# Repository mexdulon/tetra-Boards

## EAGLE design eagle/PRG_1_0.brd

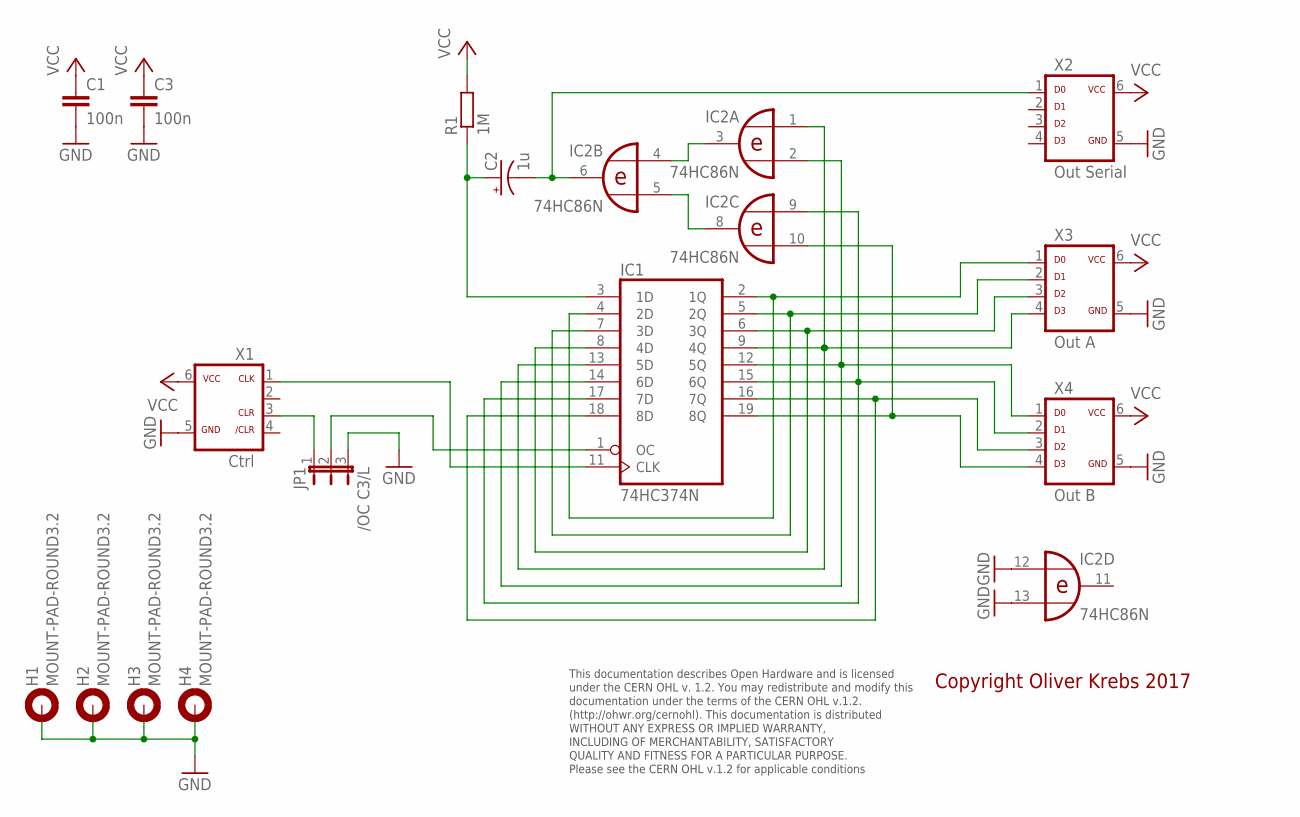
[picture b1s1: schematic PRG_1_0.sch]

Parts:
C1, C3: 100n; C050-025X075
C2: 1u; CPOL-RADIAL-10UF-25V
H1, H2, H3, H4: MOUNT-PAD-ROUND3.2; 3,2-PAD
IC1: 74HC374N; DIL20
IC2: 74HC86N; DIL14
JP1: /OC C3/L; JP2-U
R1: 1M; 0207/10
X1: Ctrl; ML-6
X2: Out Serial; ML-6
X3: Out A; ML-6
X4: Out B; ML-6

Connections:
GND: C1.2, C3.2, H1.B3,2, H2.B3,2, H3.B3,2, H4.B3,2, IC1.10 (GND), IC2.7 (GND), IC2.12 (I0), IC2.13 (I1), JP1.3, X1.5, X2.5, X3.5, X4.5
unnamed: IC2.3 (O), IC2.4 (I0)
unnamed: IC2.5 (I1), IC2.8 (O)
unnamed: C2.2 (-), IC2.6 (O), X2.1
unnamed: C2.1 (+), IC1.3 (1D), R1.1
unnamed: IC1.11 (CLK), X1.1
unnamed: IC1.1 (OC), JP1.2
unnamed: IC1.2 (1Q), IC1.4 (2D), X3.1
unnamed: IC1.5 (2Q), IC1.7 (3D), X3.2
unnamed: IC1.6 (3Q), IC1.8 (4D), X3.3
unnamed: IC1.9 (4Q), IC1.13 (5D), IC2.1 (I0), X3.4
unnamed: IC1.12 (5Q), IC1.14 (6D), IC2.2 (I1), X4.1
unnamed: IC1.15 (6Q), IC1.17 (7D), IC2.9 (I0), X4.2
unnamed: IC1.16 (7Q), IC1.18 (8D), X4.3
unnamed: IC1.19 (8Q), IC2.10 (I1), X4.4
unnamed: JP1.1, X1.3
VCC: C1.1, C3.1, IC1.20 (VCC), IC2.14 (VCC), R1.2, X1.6, X2.6, X3.6, X4.6

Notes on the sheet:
This documentation describes Open Hardware and is licensed under the CERN OHL v. 1.2. You may redistribute and modify this documentation under the terms of the CERN OHL v.1.2. (http://ohwr.org/cernohl). This documentation is distributed WITHOUT ANY EXPRESS OR IMPLIED WARRANTY, INCLUDING OF MERCHANT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
Copyright Oliver Krebs 2017

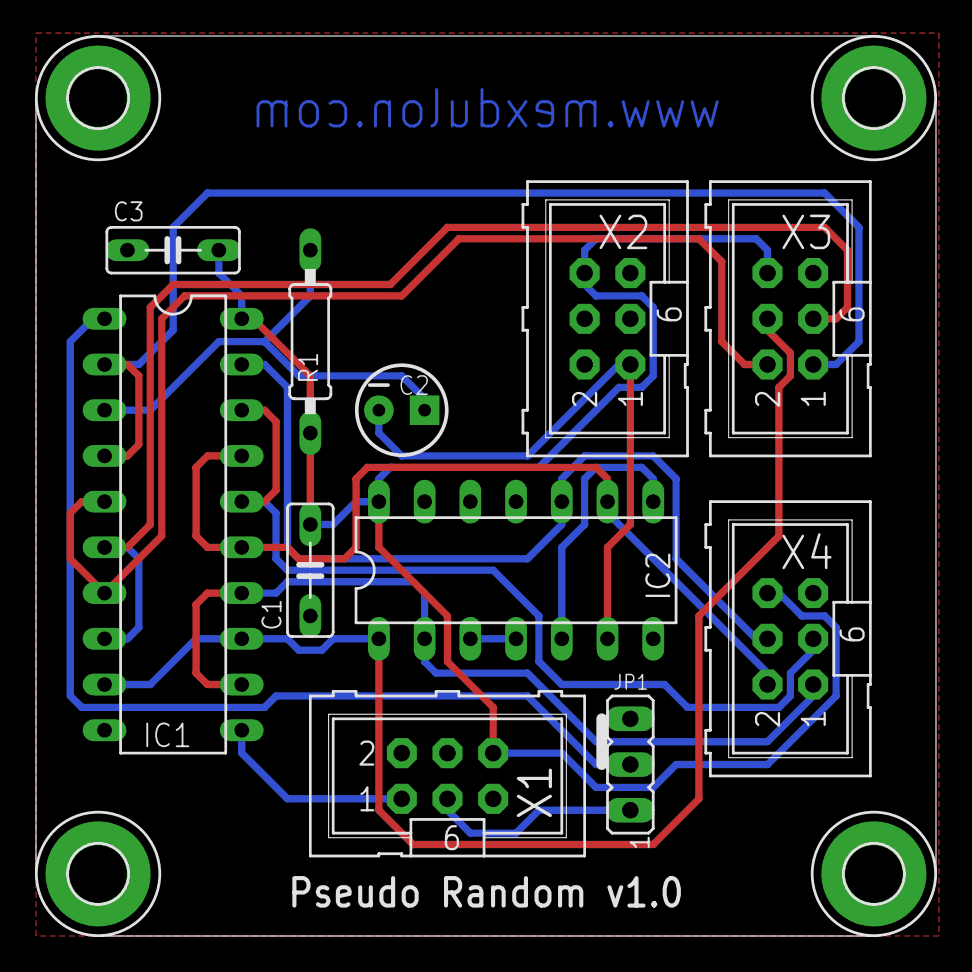
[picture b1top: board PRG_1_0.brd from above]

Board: 2 copper layers, 50.0 x 50.0 mm, 15 parts (0 on the bottom side), 17 nets.

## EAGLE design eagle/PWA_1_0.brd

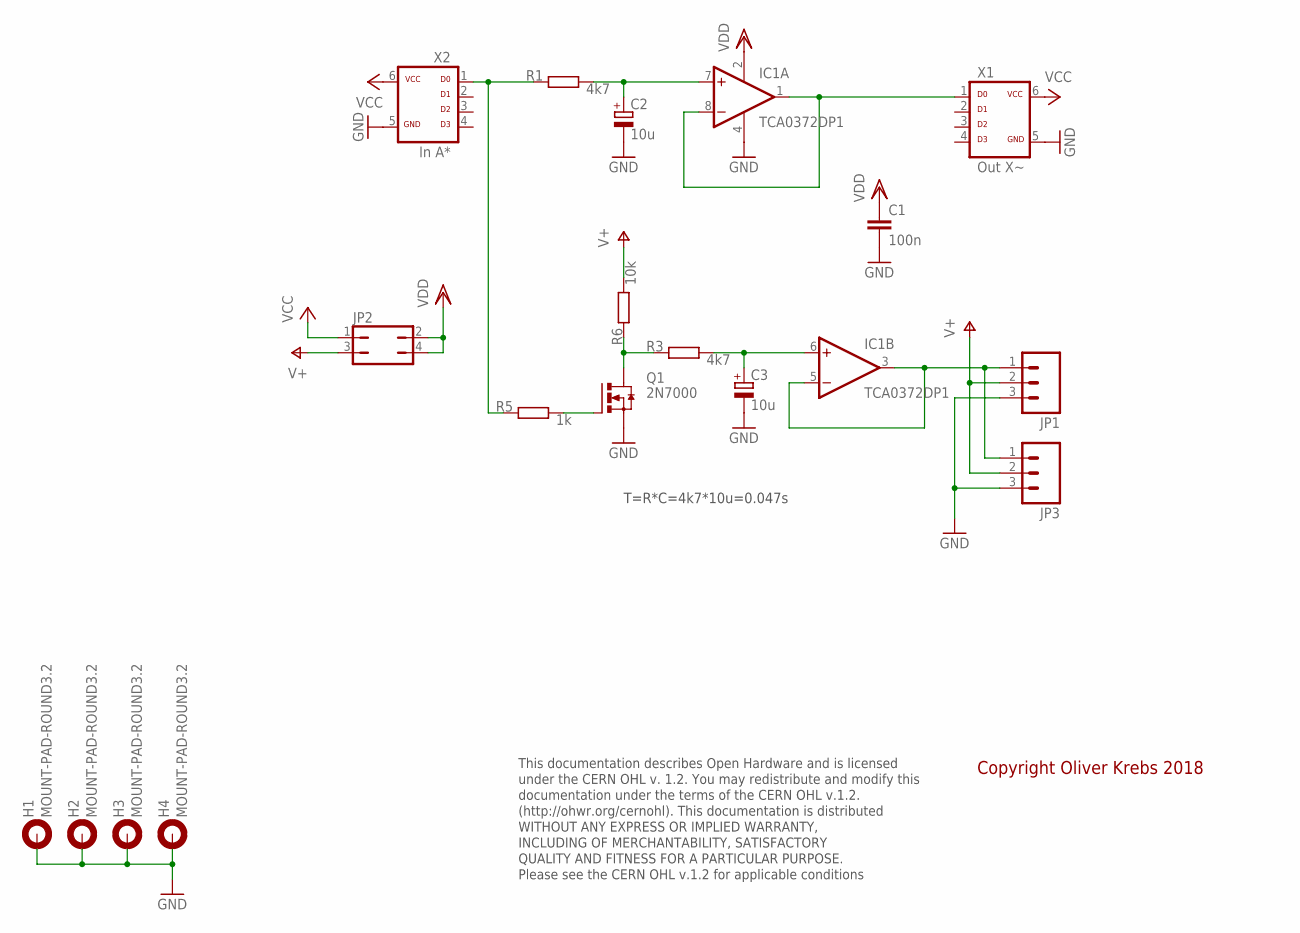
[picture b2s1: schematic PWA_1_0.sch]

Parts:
C1: 100n; C050-025X075
C2, C3: 10u; E2-4
H1, H2, H3, H4: MOUNT-PAD-ROUND3.2; 3,2-PAD
IC1: TCA0372DP1; DIL08
JP1: M03PTH; 1X03
JP2: JP2Q
JP3: M03BIG_5.08; 1X03_BIG_5.08
Q1: 2N7000; TO92-LINE
R1, R3: 4k7; 0207/10
R5: 1k; 0207/10
R6: 10k; 0207/10
X1: Out X~; ML-6
X2: In A*; ML-6

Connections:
GND: C1.2, C2.-, C3.-, H1.B3,2, H2.B3,2, H3.B3,2, H4.B3,2, IC1.4 (GND), JP1.3, JP3.3, Q1.3 (S), X1.5, X2.5
unnamed: C2.+, IC1.7 (+IN), R1.2
unnamed: IC1.1 (OUT), IC1.8 (-IN), X1.1
unnamed: R1.1, R5.1, X2.1
unnamed: IC1.3 (OUT), IC1.5 (-IN), JP1.1, JP3.1
unnamed: C3.+, IC1.6 (+IN), R3.2
unnamed: Q1.1 (D), R3.1, R6.1
unnamed: Q1.2 (G), R5.2
V+: JP1.2, JP2.3, JP3.2, R6.2
VCC: JP2.1, X1.6, X2.6
VDD: C1.1, IC1.2 (VDD), JP2.2, JP2.4

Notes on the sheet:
This documentation describes Open Hardware and is licensed under the CERN OHL v. 1.2. You may redistribute and modify this documentation under the terms of the CERN OHL v.1.2. (http://ohwr.org/cernohl). This documentation is distributed WITHOUT ANY EXPRESS OR IMPLIED WARRANTY, INCLUDING OF MERCHANT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
Copyright Oliver Krebs 2018
T=R*C=4k7*10u=0.047s

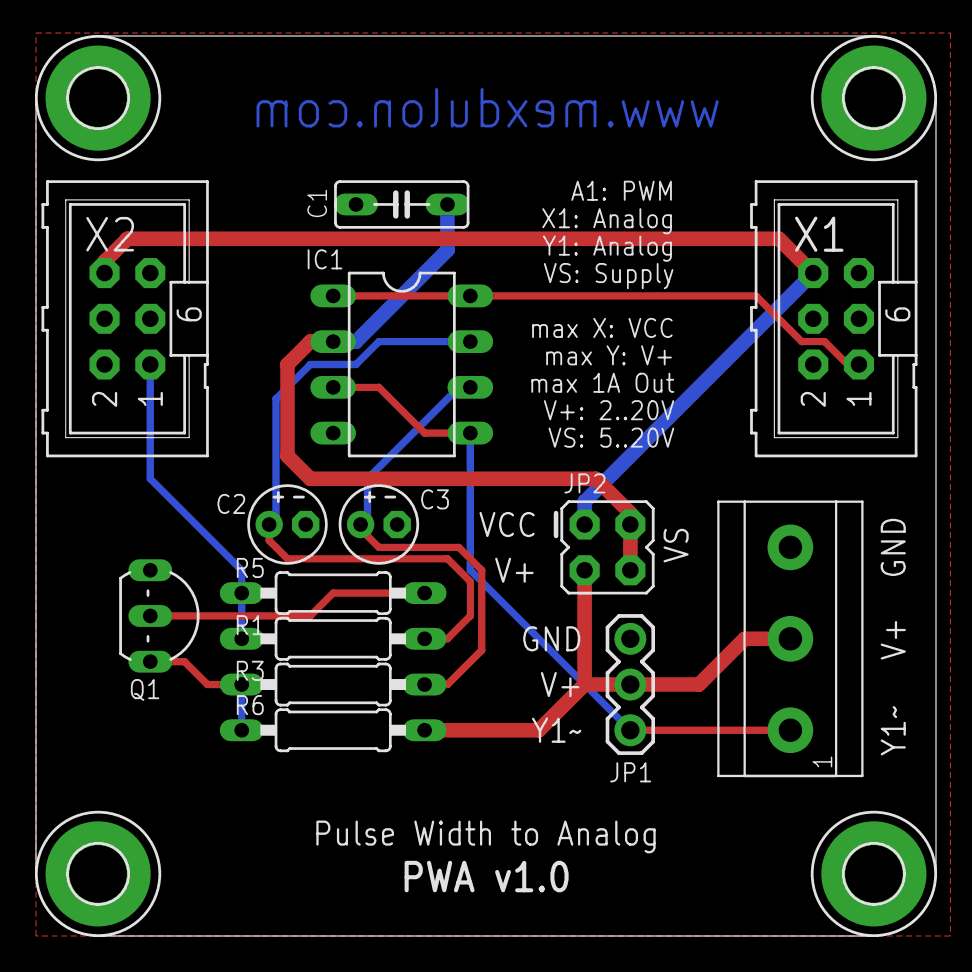
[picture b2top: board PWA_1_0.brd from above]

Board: 2 copper layers, 50.0 x 50.0 mm, 18 parts (0 on the bottom side), 11 nets.

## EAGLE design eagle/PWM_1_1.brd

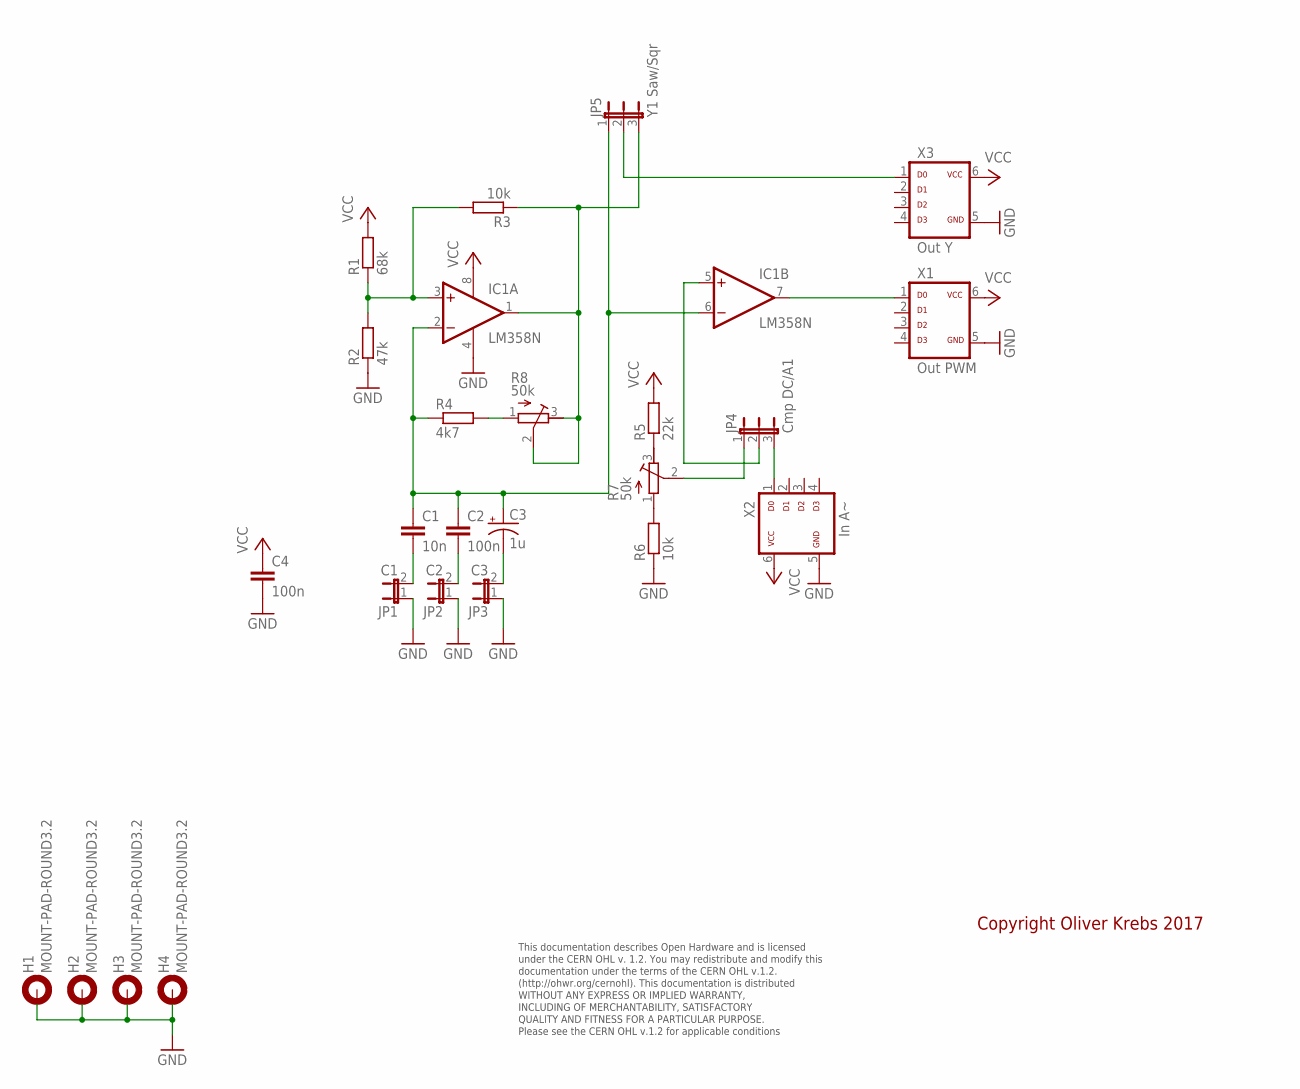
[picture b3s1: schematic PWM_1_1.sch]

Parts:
C1: 10n; C050-025X075
C2, C4: 100n; C050-025X075
C3: 1u; CPOL-RADIAL-10UF-25V
H1, H2, H3, H4: MOUNT-PAD-ROUND3.2; 3,2-PAD
IC1: LM358N; DIL08
JP1: C1; JP1
JP2: C2; JP1
JP3: C3; JP1
JP4: Cmp DC/A1; JP2-U
JP5: Y1 Saw/Sqr; JP2-U
R1: 68k; 0207/10
R2: 47k; 0207/10
R3, R6: 10k; 0207/10
R4: 4k7; 0207/10
R5: 22k; 0207/10
R7, R8: 50k; ACP-6L
X1: Out PWM; ML-6
X2: In A~; ML-6
X3: Out Y; ML-6

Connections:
GND: C4.2, H1.B3,2, H2.B3,2, H3.B3,2, H4.B3,2, IC1.4 (V-), JP1.1, JP2.1, JP3.1, R2.1, R6.1, X1.5, X2.5, X3.5
unnamed: IC1.3 (+IN), R1.1, R2.2, R3.2
unnamed: IC1.1 (OUT), JP5.3, R3.1, R8.2 (S), R8.3 (E)
unnamed: R4.2, R8.1 (A)
unnamed: C2.2, JP2.2
unnamed: C1.2, JP1.2
unnamed: C1.1, C2.1, C3.1 (+), IC1.2 (-IN), IC1.6 (-IN), JP5.1, R4.1
unnamed: C3.2 (-), JP3.2
unnamed: IC1.5 (+IN), JP4.2
unnamed: JP4.1, R7.2 (S)
unnamed: R5.1, R7.3 (E)
unnamed: R6.2, R7.1 (A)
unnamed: JP4.3, X2.1
unnamed: IC1.7 (OUT), X1.1
unnamed: JP5.2, X3.1
VCC: C4.1, IC1.8 (V+), R1.2, R5.2, X1.6, X2.6, X3.6

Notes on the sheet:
This documentation describes Open Hardware and is licensed under the CERN OHL v. 1.2. You may redistribute and modify this documentation under the terms of the CERN OHL v.1.2. (http://ohwr.org/cernohl). This documentation is distributed WITHOUT ANY EXPRESS OR IMPLIED WARRANTY, INCLUDING OF MERCHANT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
Copyright Oliver Krebs 2017

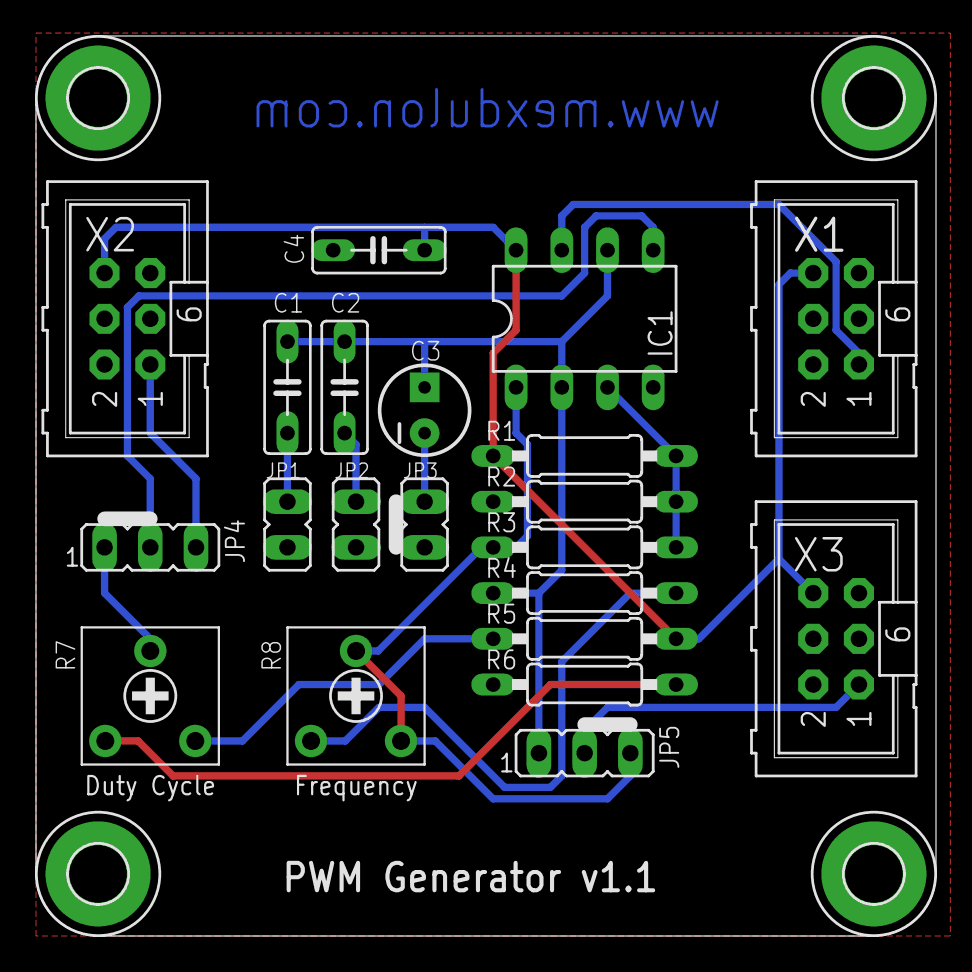
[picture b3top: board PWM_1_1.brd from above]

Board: 2 copper layers, 50.0 x 50.0 mm, 25 parts (0 on the bottom side), 16 nets.

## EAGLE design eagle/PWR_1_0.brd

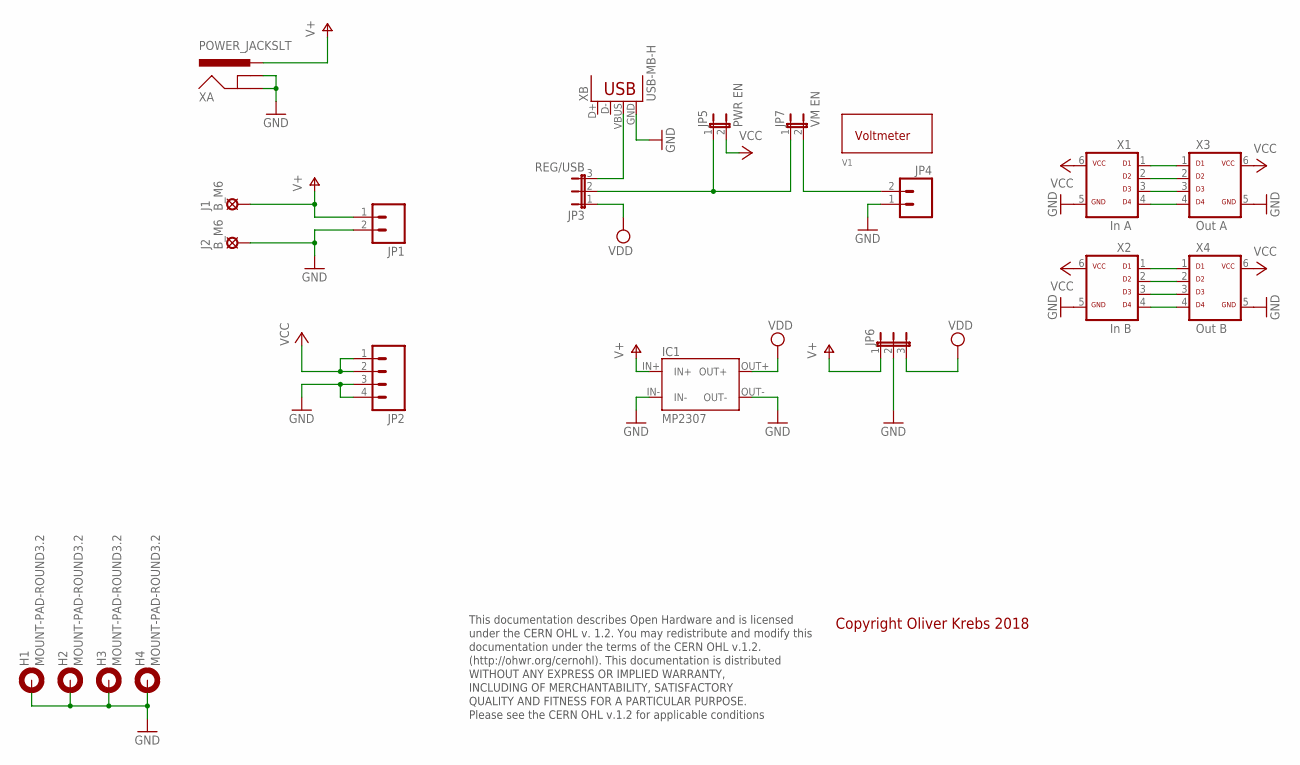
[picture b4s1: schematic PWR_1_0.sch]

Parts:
H1, H2, H3, H4: MOUNT-PAD-ROUND3.2; 3,2-PAD
IC1: MP2307
J1, J2: B_M6; BANANA_M6
JP1: M021.3MM-5.08; 1X02_BIG_5.08
JP2: M04PTH; 1X04
JP3: REG/USB; JP2-U
JP4: M02PTH; 1X02
JP5: PWR EN; JP1
JP6: JP2EJP2-U; JP2-U
JP7: VM EN; JP1
V1: VOLTMETER-28
X1: In A; ML-6
X2: In B; ML-6
X3: Out A; ML-6
X4: Out B; ML-6
XA: POWER_JACKSLT; POWER_JACK_SLOT
XB: USB-MB-H

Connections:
GND: H1.B3,2, H2.B3,2, H3.B3,2, H4.B3,2, IC1.IN-, IC1.OUT-, J2.1, JP1.2, JP2.3, JP2.4, JP4.1, JP6.2, X1.5, X2.5, X3.5, X4.5, XA.GND@1 (GNDBREAK), XA.GND@2 (GND), XB.GND
unnamed: X1.1, X3.1
unnamed: X1.2, X3.2
unnamed: X1.3, X3.3
unnamed: X1.4, X3.4
unnamed: X2.1, X4.1
unnamed: X2.2, X4.2
unnamed: X2.3, X4.3
unnamed: X2.4, X4.4
unnamed: JP3.2, JP5.1, JP7.1
unnamed: JP3.3, XB.VBUS
unnamed: JP4.2, JP7.2
V+: IC1.IN+, J1.1, JP1.1, JP6.1, XA.PWR
VCC: JP2.1, JP2.2, JP5.2, X1.6, X2.6, X3.6, X4.6
VDD: IC1.OUT+, JP3.1, JP6.3

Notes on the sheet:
This documentation describes Open Hardware and is licensed under the CERN OHL v. 1.2. You may redistribute and modify this documentation under the terms of the CERN OHL v.1.2. (http://ohwr.org/cernohl). This documentation is distributed WITHOUT ANY EXPRESS OR IMPLIED WARRANTY, INCLUDING OF MERCHANT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
Copyright Oliver Krebs 2018

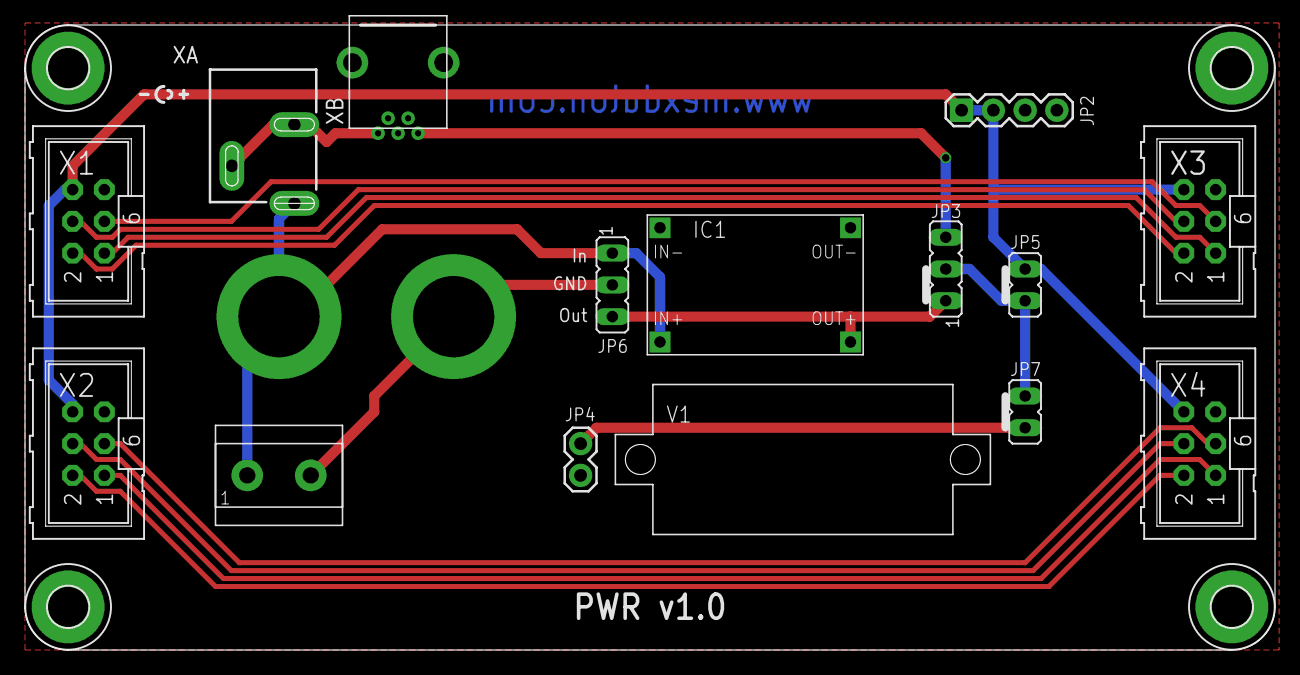
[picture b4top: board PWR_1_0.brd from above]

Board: 2 copper layers, 100.0 x 50.0 mm, 21 parts (0 on the bottom side), 15 nets.

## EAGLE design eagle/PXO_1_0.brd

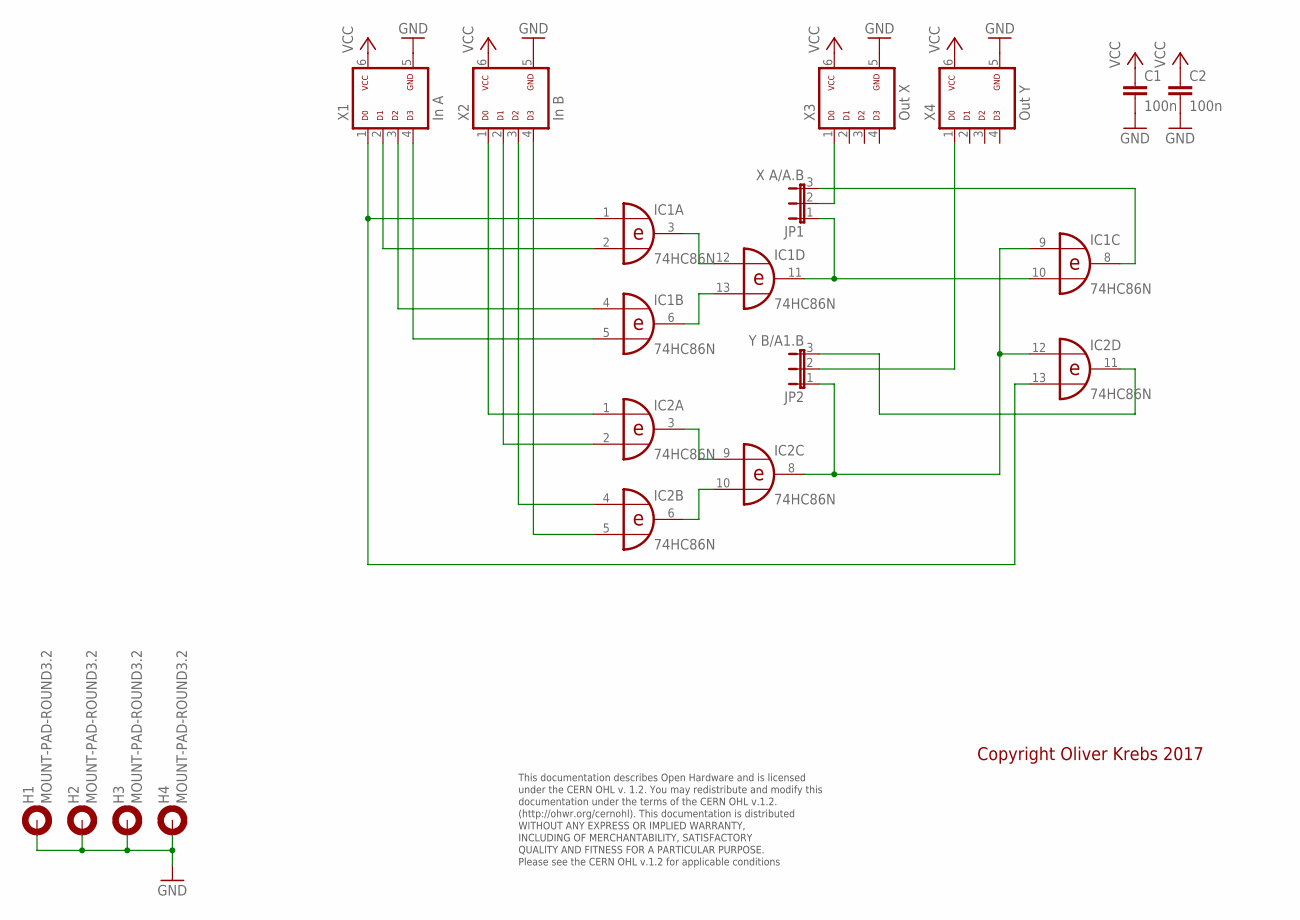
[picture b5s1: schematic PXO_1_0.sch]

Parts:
C1, C2: 100n; C050-025X075
H1, H2, H3, H4: MOUNT-PAD-ROUND3.2; 3,2-PAD
IC1, IC2: 74HC86N; DIL14
JP1: X A/A.B; JP2-U
JP2: Y B/A1.B; JP2-U
X1: In A; ML-6
X2: In B; ML-6
X3: Out X; ML-6
X4: Out Y; ML-6

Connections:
GND: C1.2, C2.2, H1.B3,2, H2.B3,2, H3.B3,2, H4.B3,2, IC1.7 (GND), IC2.7 (GND), X1.5, X2.5, X3.5, X4.5
unnamed: IC1.1 (I0), IC2.13 (I1), X1.1
unnamed: IC1.4 (I0), X1.3
unnamed: IC1.3 (O), IC1.12 (I0)
unnamed: IC1.5 (I1), X1.4
unnamed: IC1.2 (I1), X1.2
unnamed: IC1.6 (O), IC1.13 (I1)
unnamed: IC1.10 (I1), IC1.11 (O), JP1.1
unnamed: IC2.1 (I0), X2.1
unnamed: IC2.2 (I1), X2.2
unnamed: IC2.4 (I0), X2.3
unnamed: IC2.5 (I1), X2.4
unnamed: IC2.3 (O), IC2.9 (I0)
unnamed: IC2.6 (O), IC2.10 (I1)
unnamed: IC1.9 (I0), IC2.8 (O), IC2.12 (I0), JP2.1
unnamed: JP1.2, X3.1
unnamed: IC1.8 (O), JP1.3
unnamed: IC2.11 (O), JP2.3
unnamed: JP2.2, X4.1
VCC: C1.1, C2.1, IC1.14 (VCC), IC2.14 (VCC), X1.6, X2.6, X3.6, X4.6

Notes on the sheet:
This documentation describes Open Hardware and is licensed under the CERN OHL v. 1.2. You may redistribute and modify this documentation under the terms of the CERN OHL v.1.2. (http://ohwr.org/cernohl). This documentation is distributed WITHOUT ANY EXPRESS OR IMPLIED WARRANTY, INCLUDING OF MERCHANT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
Copyright Oliver Krebs 2017

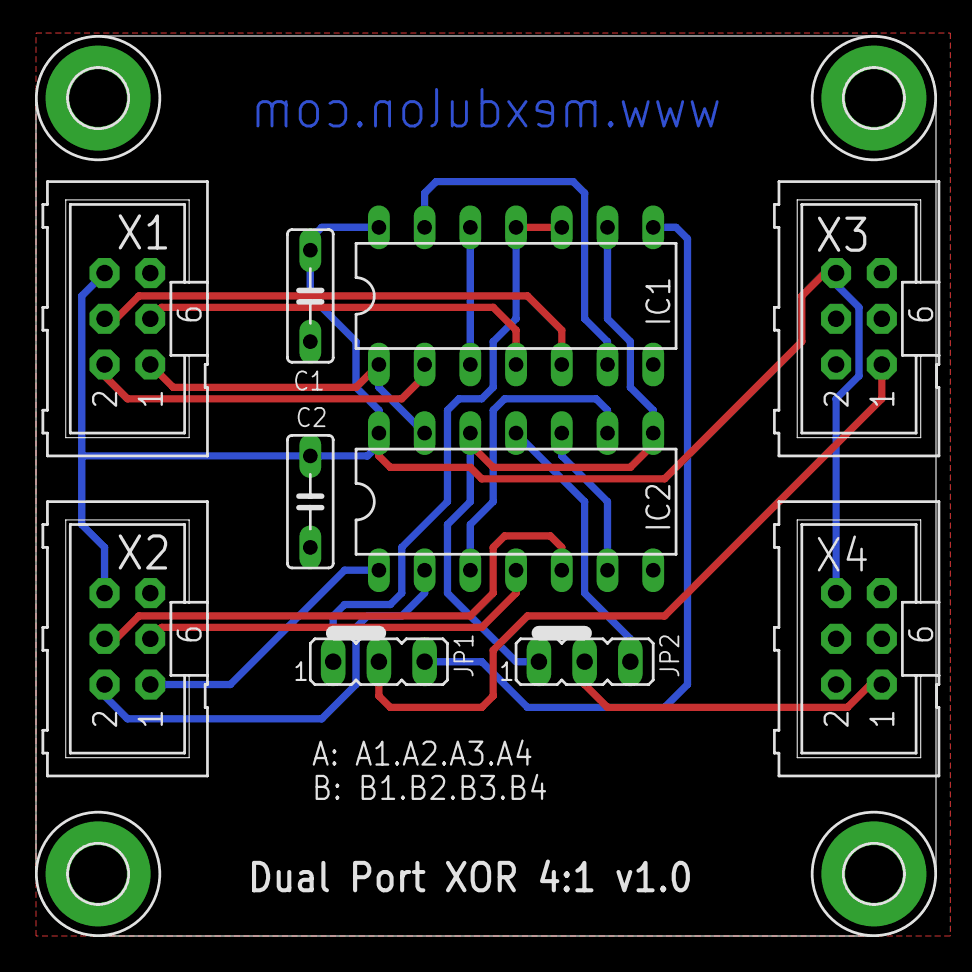
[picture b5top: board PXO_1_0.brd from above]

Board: 2 copper layers, 50.0 x 50.0 mm, 14 parts (0 on the bottom side), 20 nets.

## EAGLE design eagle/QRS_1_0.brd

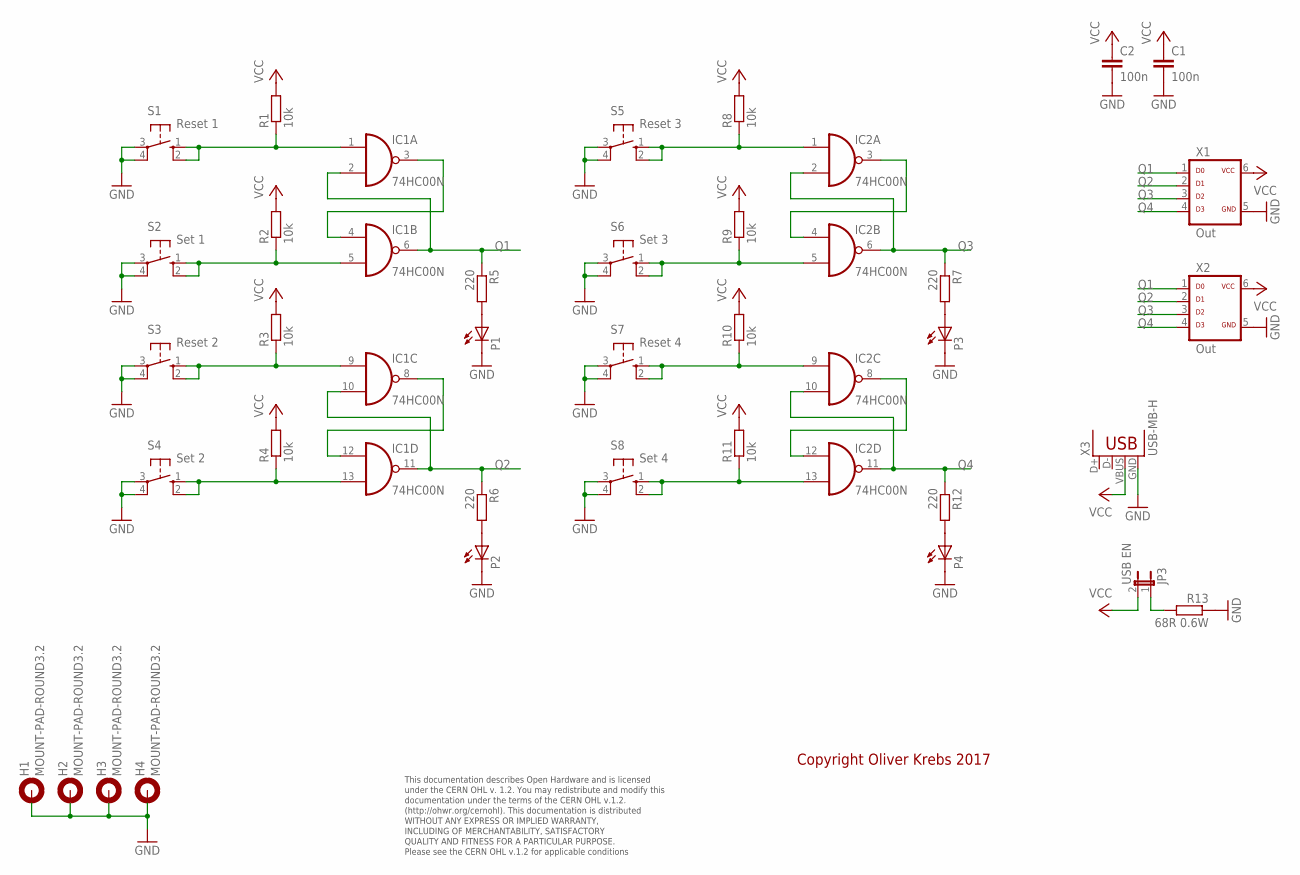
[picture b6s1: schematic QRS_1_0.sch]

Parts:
C1, C2: 100n; C050-025X075
H1, H2, H3, H4: MOUNT-PAD-ROUND3.2; 3,2-PAD
IC1, IC2: 74HC00N; DIL14
JP3: USB EN; JP1
P1, P2, P3, P4: LED3MM
R1, R2, R3, R4, R8, R9, R10, R11: 10k; 0207/10
R5, R6, R7, R12: 220; 0207/10
R13: 68R 0.6W; 0207/10
S1: Reset 1; B3F-10XX
S2: Set 1; B3F-10XX
S3: Reset 2; B3F-10XX
S4: Set 2; B3F-10XX
S5: Reset 3; B3F-10XX
S6: Set 3; B3F-10XX
S7: Reset 4; B3F-10XX
S8: Set 4; B3F-10XX
X1, X2: Out; ML-6
X3: USB-MB-H

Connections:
GND: C1.2, C2.2, H1.B3,2, H2.B3,2, H3.B3,2, H4.B3,2, IC1.7 (GND), IC2.7 (GND), P1.K (C), P2.K (C), P3.K (C), P4.K (C), R13.1, S1.3, S1.4 (P1), S2.3, S2.4 (P1), S3.3, S3.4 (P1), S4.3, S4.4 (P1), S5.3, S5.4 (P1), S6.3, S6.4 (P1), S7.3, S7.4 (P1), S8.3, S8.4 (P1), X1.5, X2.5, X3.GND
unnamed: IC1.1 (I0), R1.1, S1.1 (S), S1.2 (S1)
unnamed: JP3.1, R13.2
unnamed: IC1.3 (O), IC1.4 (I0)
unnamed: IC1.5 (I1), R2.1, S2.1 (S), S2.2 (S1)
unnamed: IC1.9 (I0), R3.1, S3.1 (S), S3.2 (S1)
unnamed: IC1.13 (I1), R4.1, S4.1 (S), S4.2 (S1)
unnamed: IC1.8 (O), IC1.12 (I0)
unnamed: P1.A, R5.2
unnamed: P2.A, R6.2
unnamed: IC2.1 (I0), R8.1, S5.1 (S), S5.2 (S1)
unnamed: IC2.5 (I1), R9.1, S6.1 (S), S6.2 (S1)
unnamed: IC2.9 (I0), R10.1, S7.1 (S), S7.2 (S1)
unnamed: P3.A, R7.2
unnamed: IC2.3 (O), IC2.4 (I0)
unnamed: IC2.13 (I1), R11.1, S8.1 (S), S8.2 (S1)
unnamed: IC2.8 (O), IC2.12 (I0)
unnamed: P4.A, R12.2
Q1: IC1.2 (I1), IC1.6 (O), R5.1, X1.1, X2.1
Q2: IC1.10 (I1), IC1.11 (O), R6.1, X1.2, X2.2
Q3: IC2.2 (I1), IC2.6 (O), R7.1, X1.3, X2.3
Q4: IC2.10 (I1), IC2.11 (O), R12.1, X1.4, X2.4
VCC: C1.1, C2.1, IC1.14 (VCC), IC2.14 (VCC), JP3.2, R1.2, R2.2, R3.2, R4.2, R8.2, R9.2, R10.2, R11.2, X1.6, X2.6, X3.VBUS

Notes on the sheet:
This documentation describes Open Hardware and is licensed under the CERN OHL v. 1.2. You may redistribute and modify this documentation under the terms of the CERN OHL v.1.2. (http://ohwr.org/cernohl). This documentation is distributed WITHOUT ANY EXPRESS OR IMPLIED WARRANTY, INCLUDING OF MERCHANT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
Copyright Oliver Krebs 2017

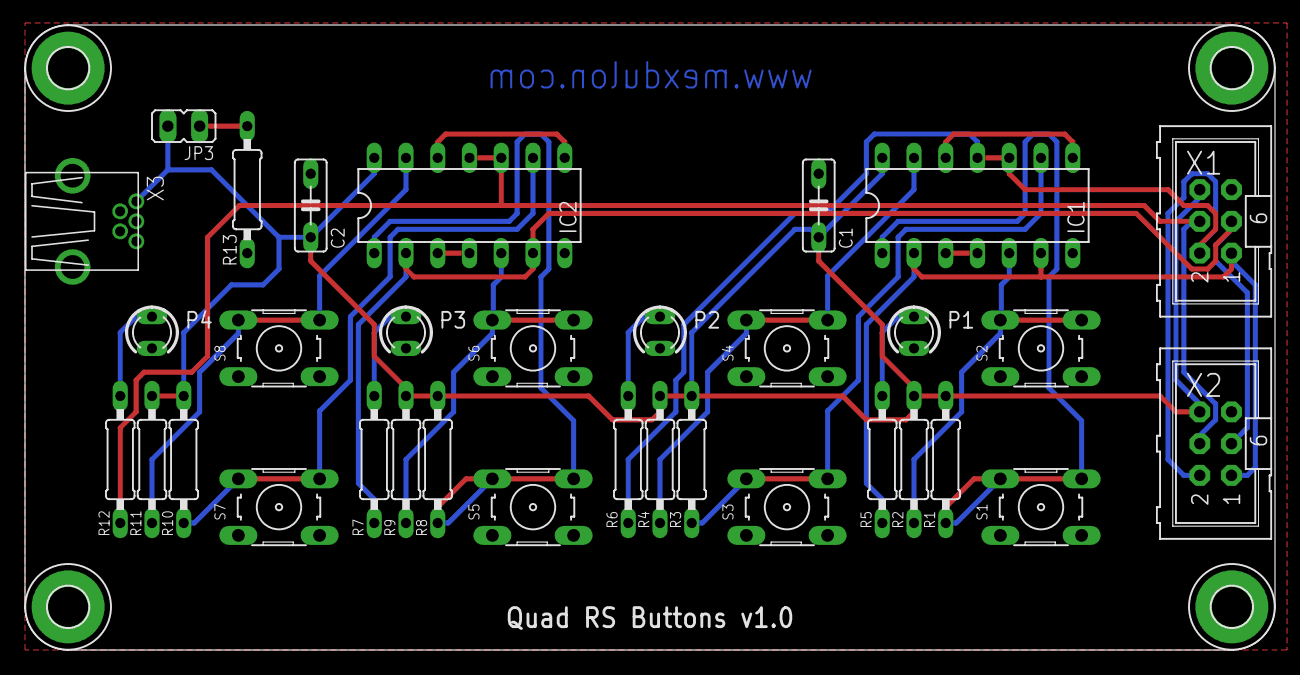
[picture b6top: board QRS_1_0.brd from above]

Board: 2 copper layers, 100.0 x 50.0 mm, 37 parts (0 on the bottom side), 23 nets.

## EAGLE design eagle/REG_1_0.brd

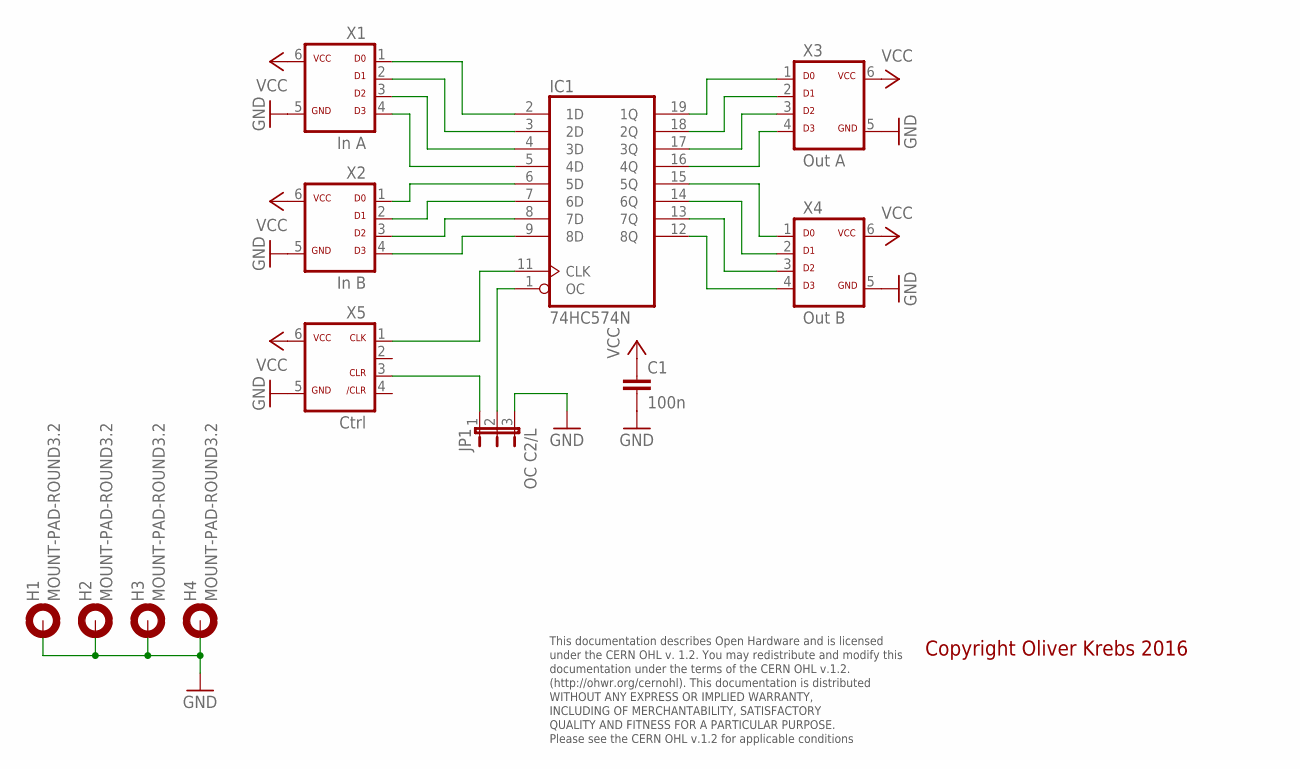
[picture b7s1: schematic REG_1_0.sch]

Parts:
C1: 100n; C050-025X075
H1, H2, H3, H4: MOUNT-PAD-ROUND3.2; 3,2-PAD
IC1: 74HC574N; DIL20
JP1: OC C2/L; JP2
X1: In A; ML-6
X2: In B; ML-6
X3: Out A; ML-6
X4: Out B; ML-6
X5: Ctrl; ML-6

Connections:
GND: C1.2, H1.B3,2, H2.B3,2, H3.B3,2, H4.B3,2, IC1.10 (GND), JP1.3, X1.5, X2.5, X3.5, X4.5, X5.5
unnamed: IC1.2 (1D), X1.1
unnamed: IC1.3 (2D), X1.2
unnamed: IC1.4 (3D), X1.3
unnamed: IC1.5 (4D), X1.4
unnamed: IC1.6 (5D), X2.1
unnamed: IC1.7 (6D), X2.2
unnamed: IC1.8 (7D), X2.3
unnamed: IC1.9 (8D), X2.4
unnamed: IC1.11 (CLK), X5.1
unnamed: IC1.1 (OC), JP1.2
unnamed: IC1.19 (1Q), X3.1
unnamed: IC1.18 (2Q), X3.2
unnamed: IC1.17 (3Q), X3.3
unnamed: IC1.16 (4Q), X3.4
unnamed: IC1.15 (5Q), X4.1
unnamed: IC1.14 (6Q), X4.2
unnamed: IC1.13 (7Q), X4.3
unnamed: IC1.12 (8Q), X4.4
unnamed: JP1.1, X5.3
VCC: C1.1, IC1.20 (VCC), X1.6, X2.6, X3.6, X4.6, X5.6

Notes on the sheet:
This documentation describes Open Hardware and is licensed under the CERN OHL v. 1.2. You may redistribute and modify this documentation under the terms of the CERN OHL v.1.2. (http://ohwr.org/cernohl). This documentation is distributed WITHOUT ANY EXPRESS OR IMPLIED WARRANTY, INCLUDING OF MERCHANT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
Copyright Oliver Krebs 2016

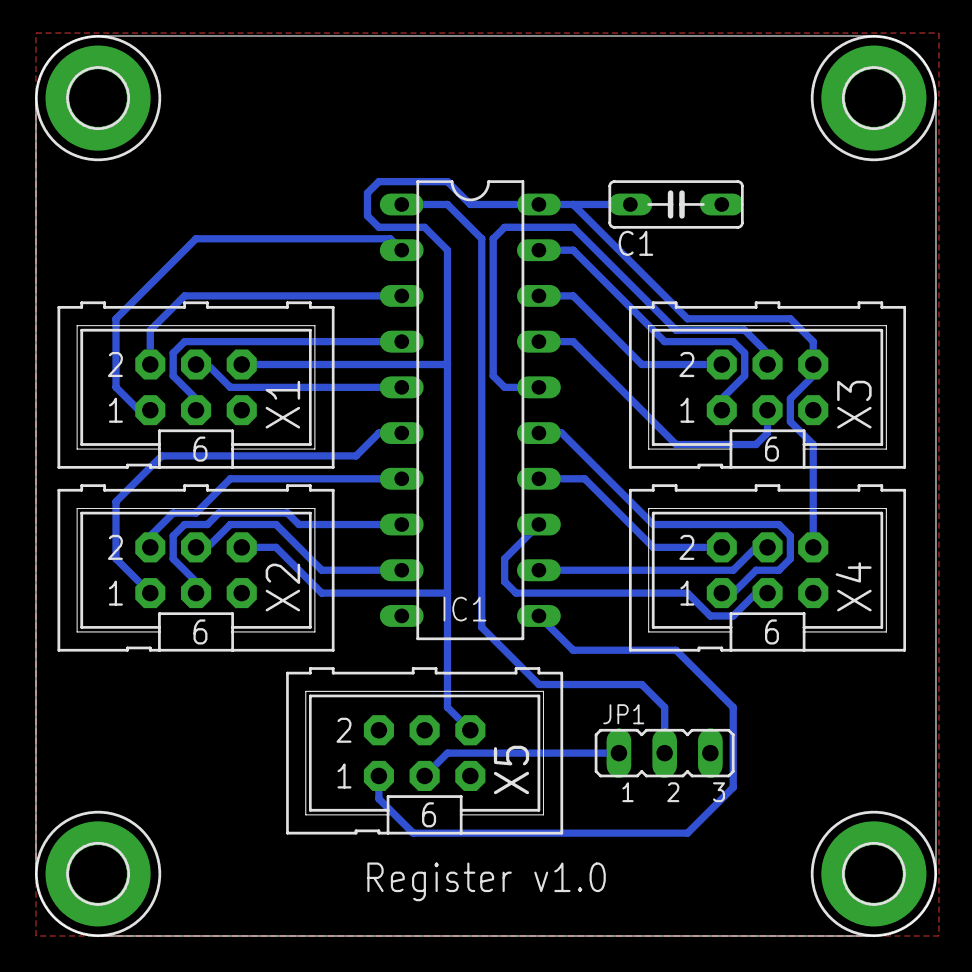
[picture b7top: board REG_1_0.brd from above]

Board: 2 copper layers, 50.0 x 50.0 mm, 12 parts (0 on the bottom side), 21 nets.

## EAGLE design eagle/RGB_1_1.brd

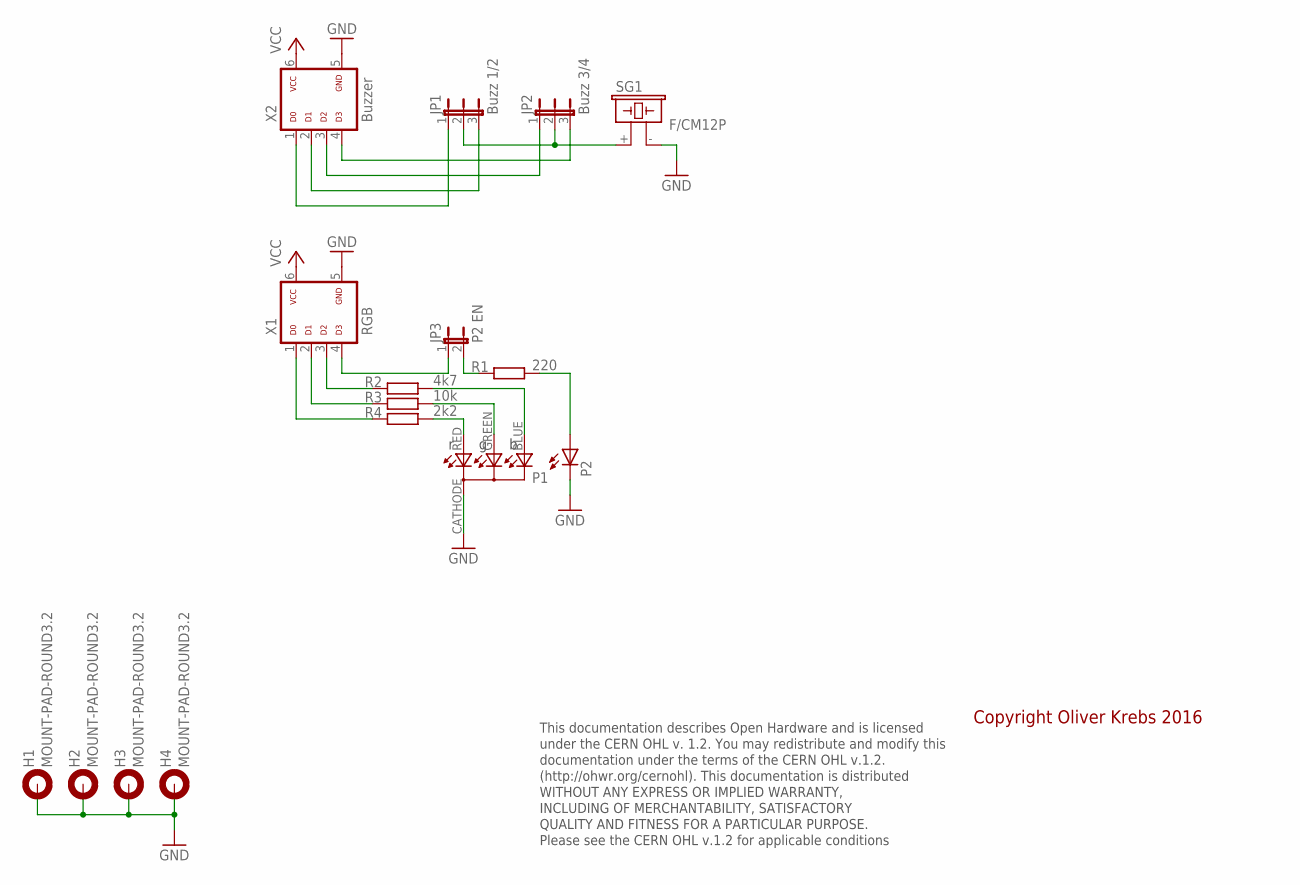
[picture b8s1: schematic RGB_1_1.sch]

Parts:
H1, H2, H3, H4: MOUNT-PAD-ROUND3.2; 3,2-PAD
JP1: Buzz 1/2; JP2
JP2: Buzz 3/4; JP2
JP3: P2 EN; JP1
P1: RGB-5MM; RGB5MM
P2: LED5MM
R1: 220; 0207/10
R2: 4k7; 0207/10
R3: 10k; 0207/10
R4: 2k2; 0207/10
SG1: F/CM12P
X1: RGB; ML-6
X2: Buzzer; ML-6

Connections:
GND: H1.B3,2, H2.B3,2, H3.B3,2, H4.B3,2, P1.CATHODE, P2.K (C), SG1.- (2), X1.5, X2.5
unnamed: JP1.2, JP2.2, SG1.+ (1)
unnamed: JP3.1, X1.4
unnamed: JP1.1, X2.1
unnamed: JP1.3, X2.2
unnamed: JP2.1, X2.3
unnamed: JP2.3, X2.4
unnamed: R2.1, X1.3
unnamed: R4.1, X1.1
unnamed: R3.1, X1.2
unnamed: P1.RED (A-RED), R4.2
unnamed: P1.GREEN (A-GREEN), R3.2
unnamed: P1.BLUE (A-BLUE), R2.2
unnamed: P2.A, R1.2
unnamed: JP3.2, R1.1
VCC: X1.6, X2.6

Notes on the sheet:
This documentation describes Open Hardware and is licensed under the CERN OHL v. 1.2. You may redistribute and modify this documentation under the terms of the CERN OHL v.1.2. (http://ohwr.org/cernohl). This documentation is distributed WITHOUT ANY EXPRESS OR IMPLIED WARRANTY, INCLUDING OF MERCHANT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
Copyright Oliver Krebs 2016

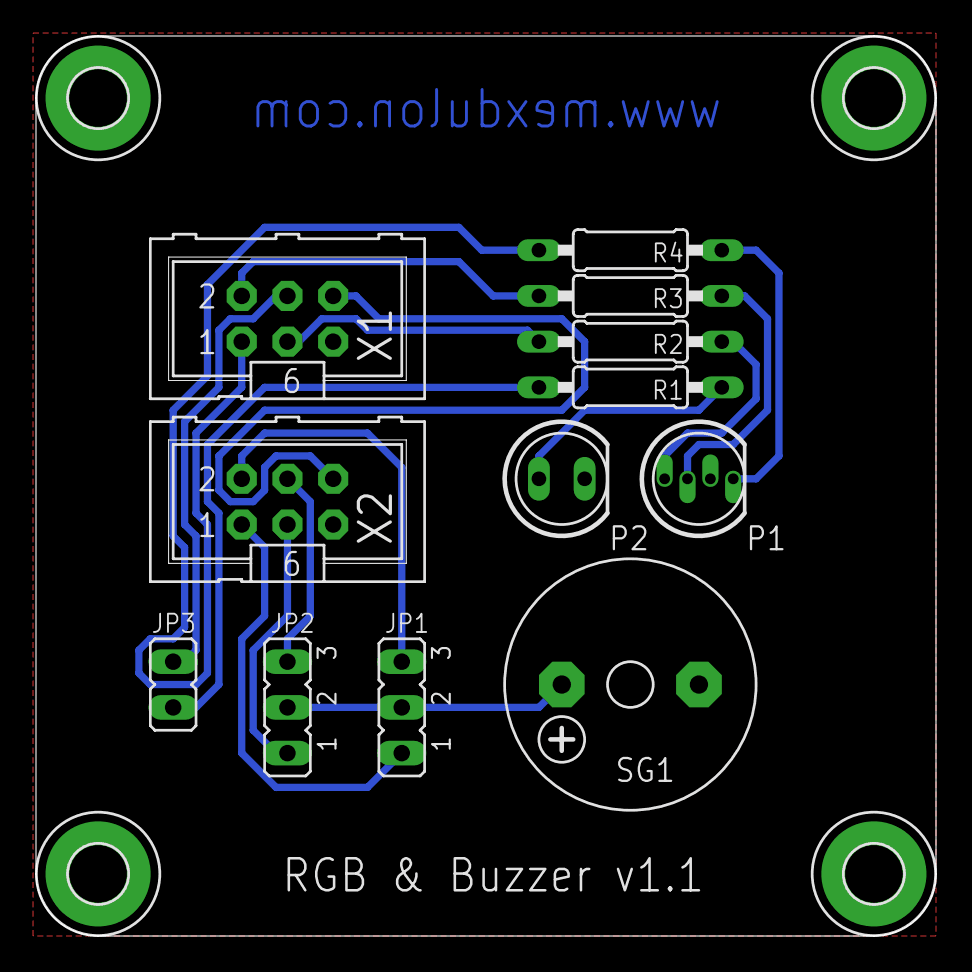
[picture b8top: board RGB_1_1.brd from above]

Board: 2 copper layers, 50.0 x 50.0 mm, 16 parts (0 on the bottom side), 16 nets.

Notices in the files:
eagle/PRG_1_0.brd:
Licensed under CERN OHL v.1.2
parts and their libraries:
SparkFun-Passives: Licensing: Creative Commons ShareAlike 4.0 International - https://creativecommons.org/licenses/by-sa/4.0
